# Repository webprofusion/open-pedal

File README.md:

# open-pedal

A cheap, open-source guitar audio dock: a USB-C class-compliant audio interface for any phone or tablet, with footswitches for bank and preset selection and an expression pedal input.

- Instrument in, stereo line out and a 6.35 mm headphone out
- 24-bit, 48 kHz USB audio (1 in, 2 out) plus USB MIDI on one cable
- Six footswitches: Bank −, Bank +, presets A to D
- RP2040, PCM1808 ADC, PCM5102A DAC; about US$52 in parts

The images are renders of the enclosure model, not photos.

Status: design stage. Nothing has been built or measured yet.

See [docs/design.md](docs/design.md) for the full hardware design.

## Layout

- `docs/`: design document and block diagram
- `hardware/`: pin map, schematic notes, BOM and `layout.json` (mechanical layout)
- `hardware/kicad/`: KiCad 10 project, generated by script: schematic and a placed, unrouted board
- `enclosure/`: Blender model of the enclosure, generated by script, with renders
- `firmware/`: RP2040 firmware (USB MIDI foot controller so far; audio not implemented)

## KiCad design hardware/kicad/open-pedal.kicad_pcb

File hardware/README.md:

# Hardware

Design inputs and the KiCad project for the open-pedal dock board. Nothing here has been built or measured.

- `pinmap.md`: RP2040 GPIO assignment (matches `firmware/src/pins.h`)
- `schematic-notes.md`: block-by-block connections and part values
- `bom.csv`: bill of materials with approximate prices
- `layout.json`: mechanical layout (enclosure, switch and rear-panel positions, device holder), shared by the board generator and the Blender enclosure model in `../enclosure/`
- `kicad/`: KiCad 10 project

See `../docs/design.md` for the reasoning behind the part choices.

## KiCad project

`kicad/open-pedal.kicad_pro` opens in KiCad 10. The schematic and board are generated from two files, so edit those and rebuild instead of editing the sheet by hand:

- `kicad/scripts/design.py`: every part, value, footprint and net
- `layout.json`: board size and where the connectors, headers and holes sit

Rebuild with the Python that ships with KiCad (it provides `pcbnew`):

```
"<KiCad 10>/bin/python" hardware/kicad/scripts/build.py
```

The build writes the schematic, runs ERC, exports KiCad's netlist and compares it pin by pin with `design.py`, writes the board, runs DRC, and exports a schematic PDF, a board render and a board GLB to `kicad/exports/`. It fails on any ERC violation, any netlist difference, or any DRC violation other than unrouted nets and silkscreen overlaps.

What is there:

- **Schematic**: 159 parts, 111 nets, one sheet. It is drawn netlist-style: parts are grouped by block and each pin carries a net label, so connections are by name and not by drawn wire.
- **Board**: 176 x 72 mm outline, 4 copper layers, every footprint placed with its nets assigned. Rear-panel connectors, switch headers and mounting holes are at their `layout.json` positions. The remaining parts are packed by block as a starting point.

What is not there:

- No routing, planes, stackup or design rules beyond KiCad's defaults. Decoupling capacitors are grouped with their block, not yet next to their pins.
- KiCad ships no 3D models for the Neutrik jacks and Alps pots, so they are missing from the board render. The Blender model draws stand-ins.

## Choices made at capture

`schematic-notes.md` leaves some parts open. The schematic picks these; all are unverified against current datasheets:

| Block | Choice |
| --- | --- |
| Boost converter | TPS61040, 10 uH, 360 k / 100 k feedback for about 5.7 V |
| 5 V analog LDO | TPS7A2050 (6.0 V maximum input, so the boost voltage must stay below that) |
| 3.3 V LDOs | AP2112K-3.3 (digital), LP5907-3.3 (analog) |
| 5 V input OR | Two B5819W Schottky diodes |
| Jacks | Neutrik NMJ4HCD2 (mono, switched) and NMJ6HCD2 (stereo, switched) |
| Pots | Alps RK09K (gain), RK09L dual (volume) |
| USB-C | GCT USB4105 (host), GCT USB4125 (power only) |
| Headphone amp | TPA6132A2, single-ended inputs, G0 = G1 = low for the lowest gain |
| Input jack | Tip switch contact to ground, so the input is shorted with nothing plugged in |
| R output detect | Sleeve switch contact to GPIO 7; reads high when a plug is in |
| Footswitches | Momentary with a single-colour LED ring, 12 mm bushing assumed; no particular part chosen |
| LED ring drive | V5 through 150 ohm, 2N7002 low-side switch per ring from GPIO 16 to 21 |
| Footswitch and OLED leads | JST XH headers, four-way |

The PCM1808 pin numbers in the project symbol library are from memory. Check them, and every pin strap, against the datasheets before ordering boards.

## To do

1. Breadboard proof with a Pico, a PCM1808 module and a PCM5102A module, wired to `pinmap.md`.
2. Check every symbol pin and strap against the current datasheets.
3. Confirm the connector heights in `layout.json` against the parts bought; they set the rear-panel drilling.
4. Place decoupling, route the 4-layer board, add ground planes and stackup.

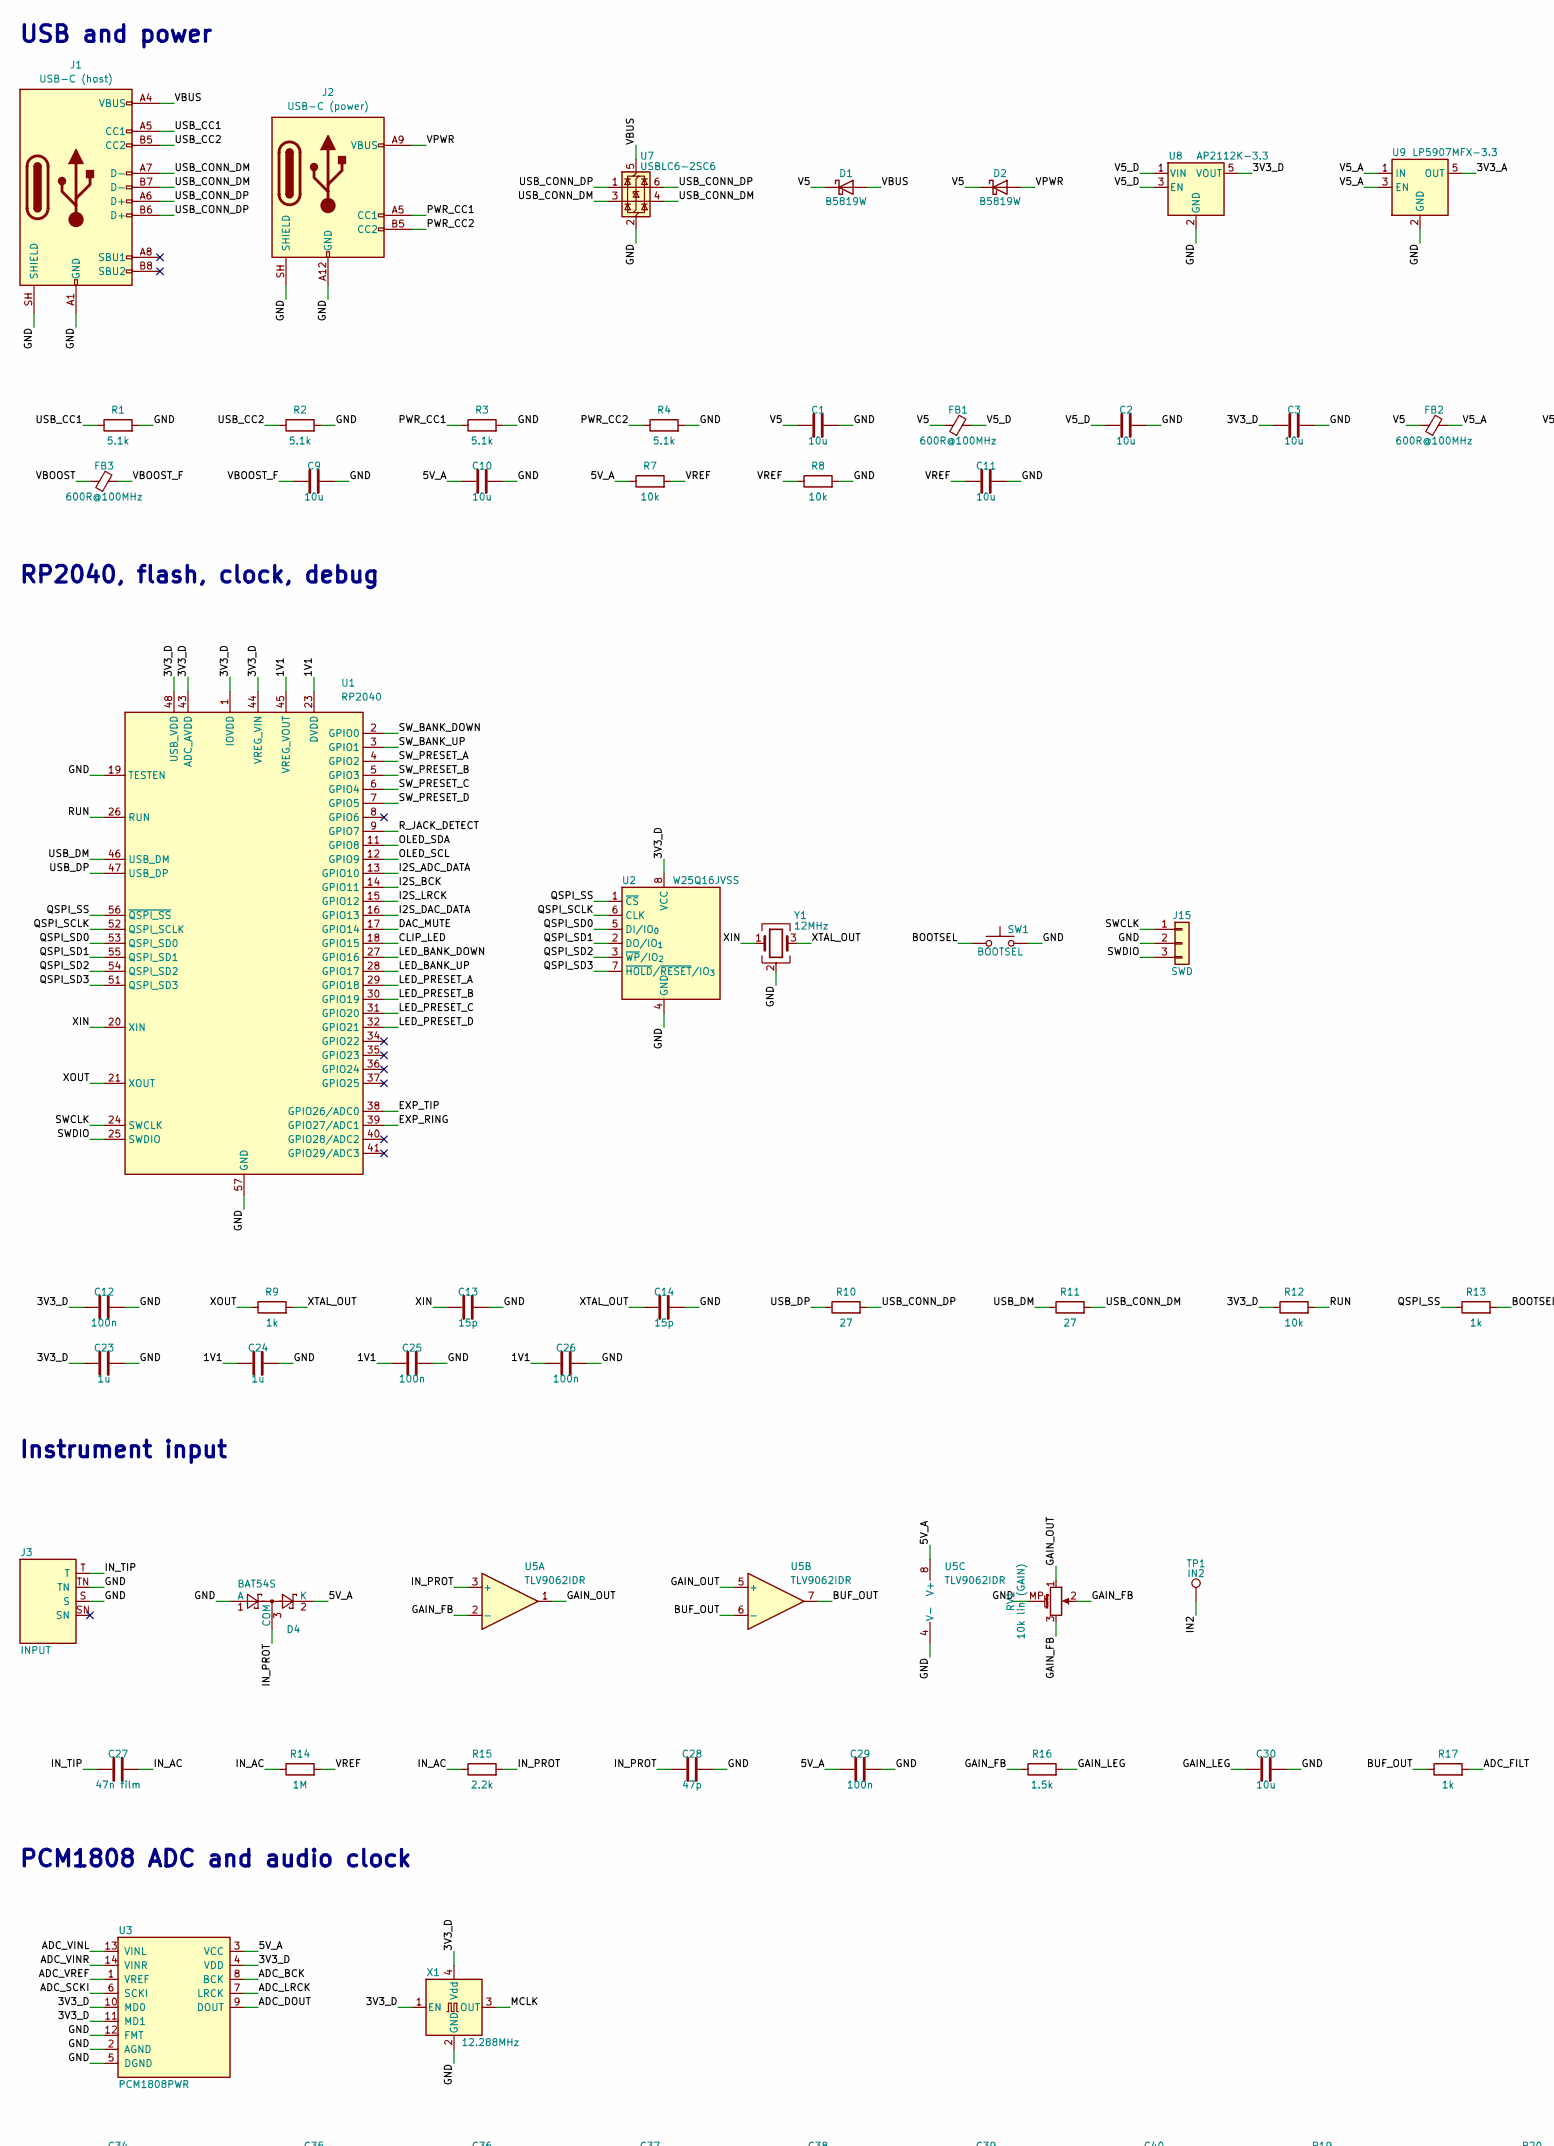
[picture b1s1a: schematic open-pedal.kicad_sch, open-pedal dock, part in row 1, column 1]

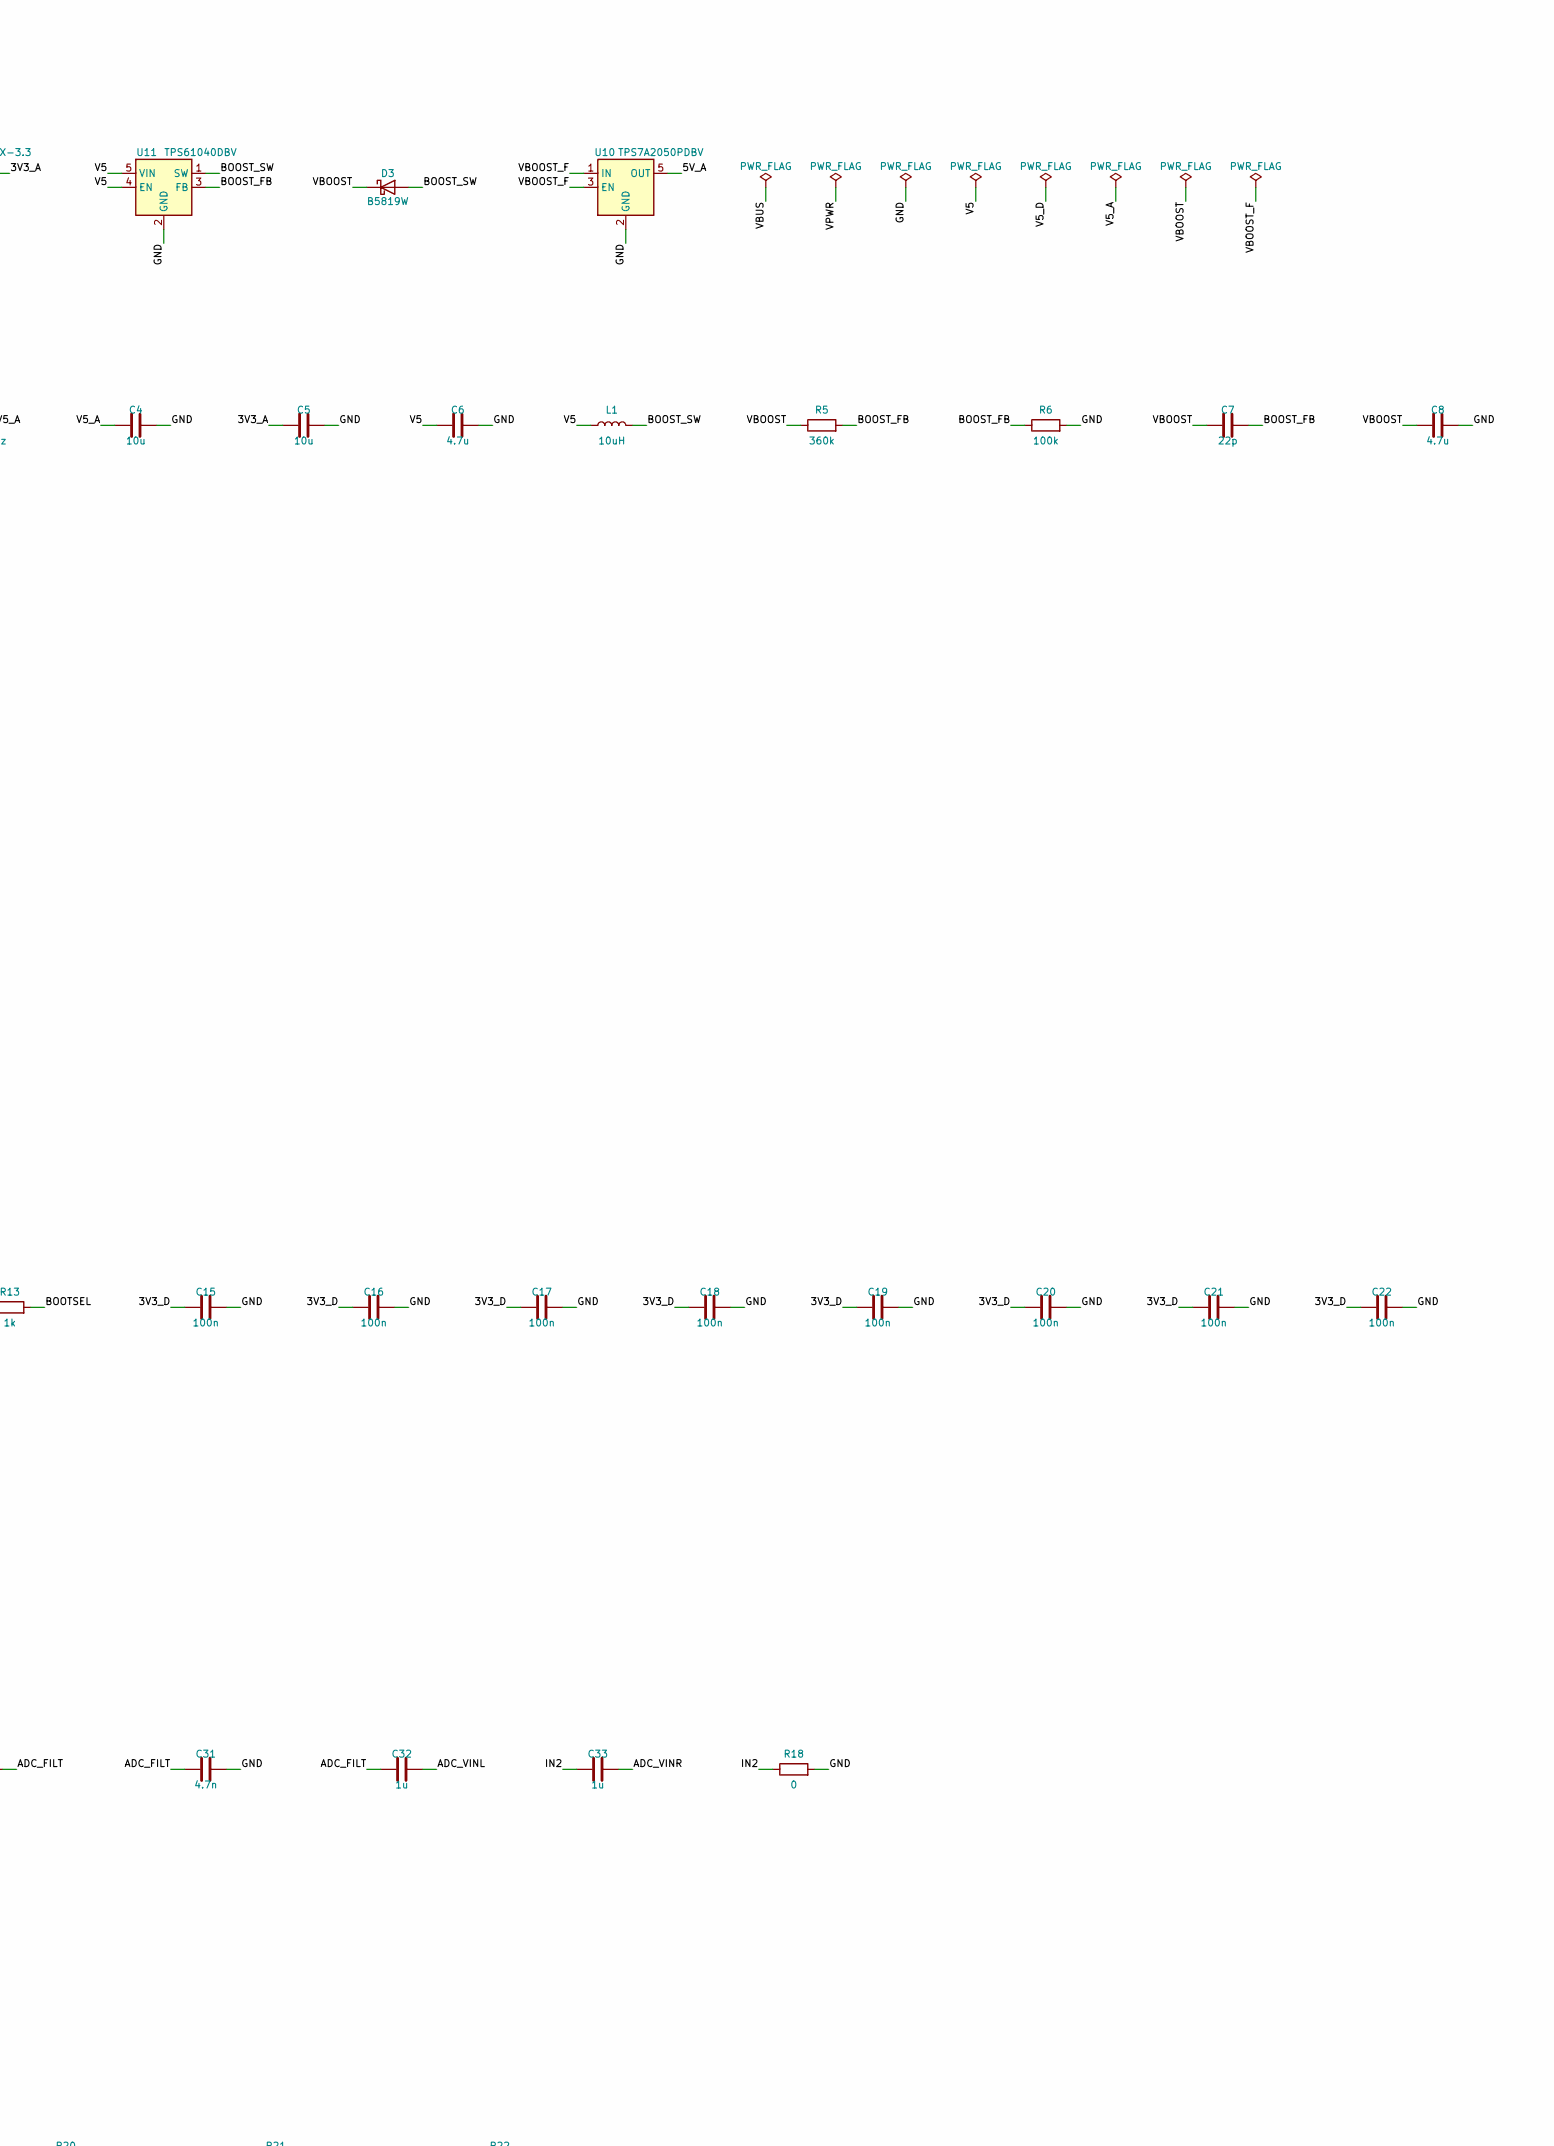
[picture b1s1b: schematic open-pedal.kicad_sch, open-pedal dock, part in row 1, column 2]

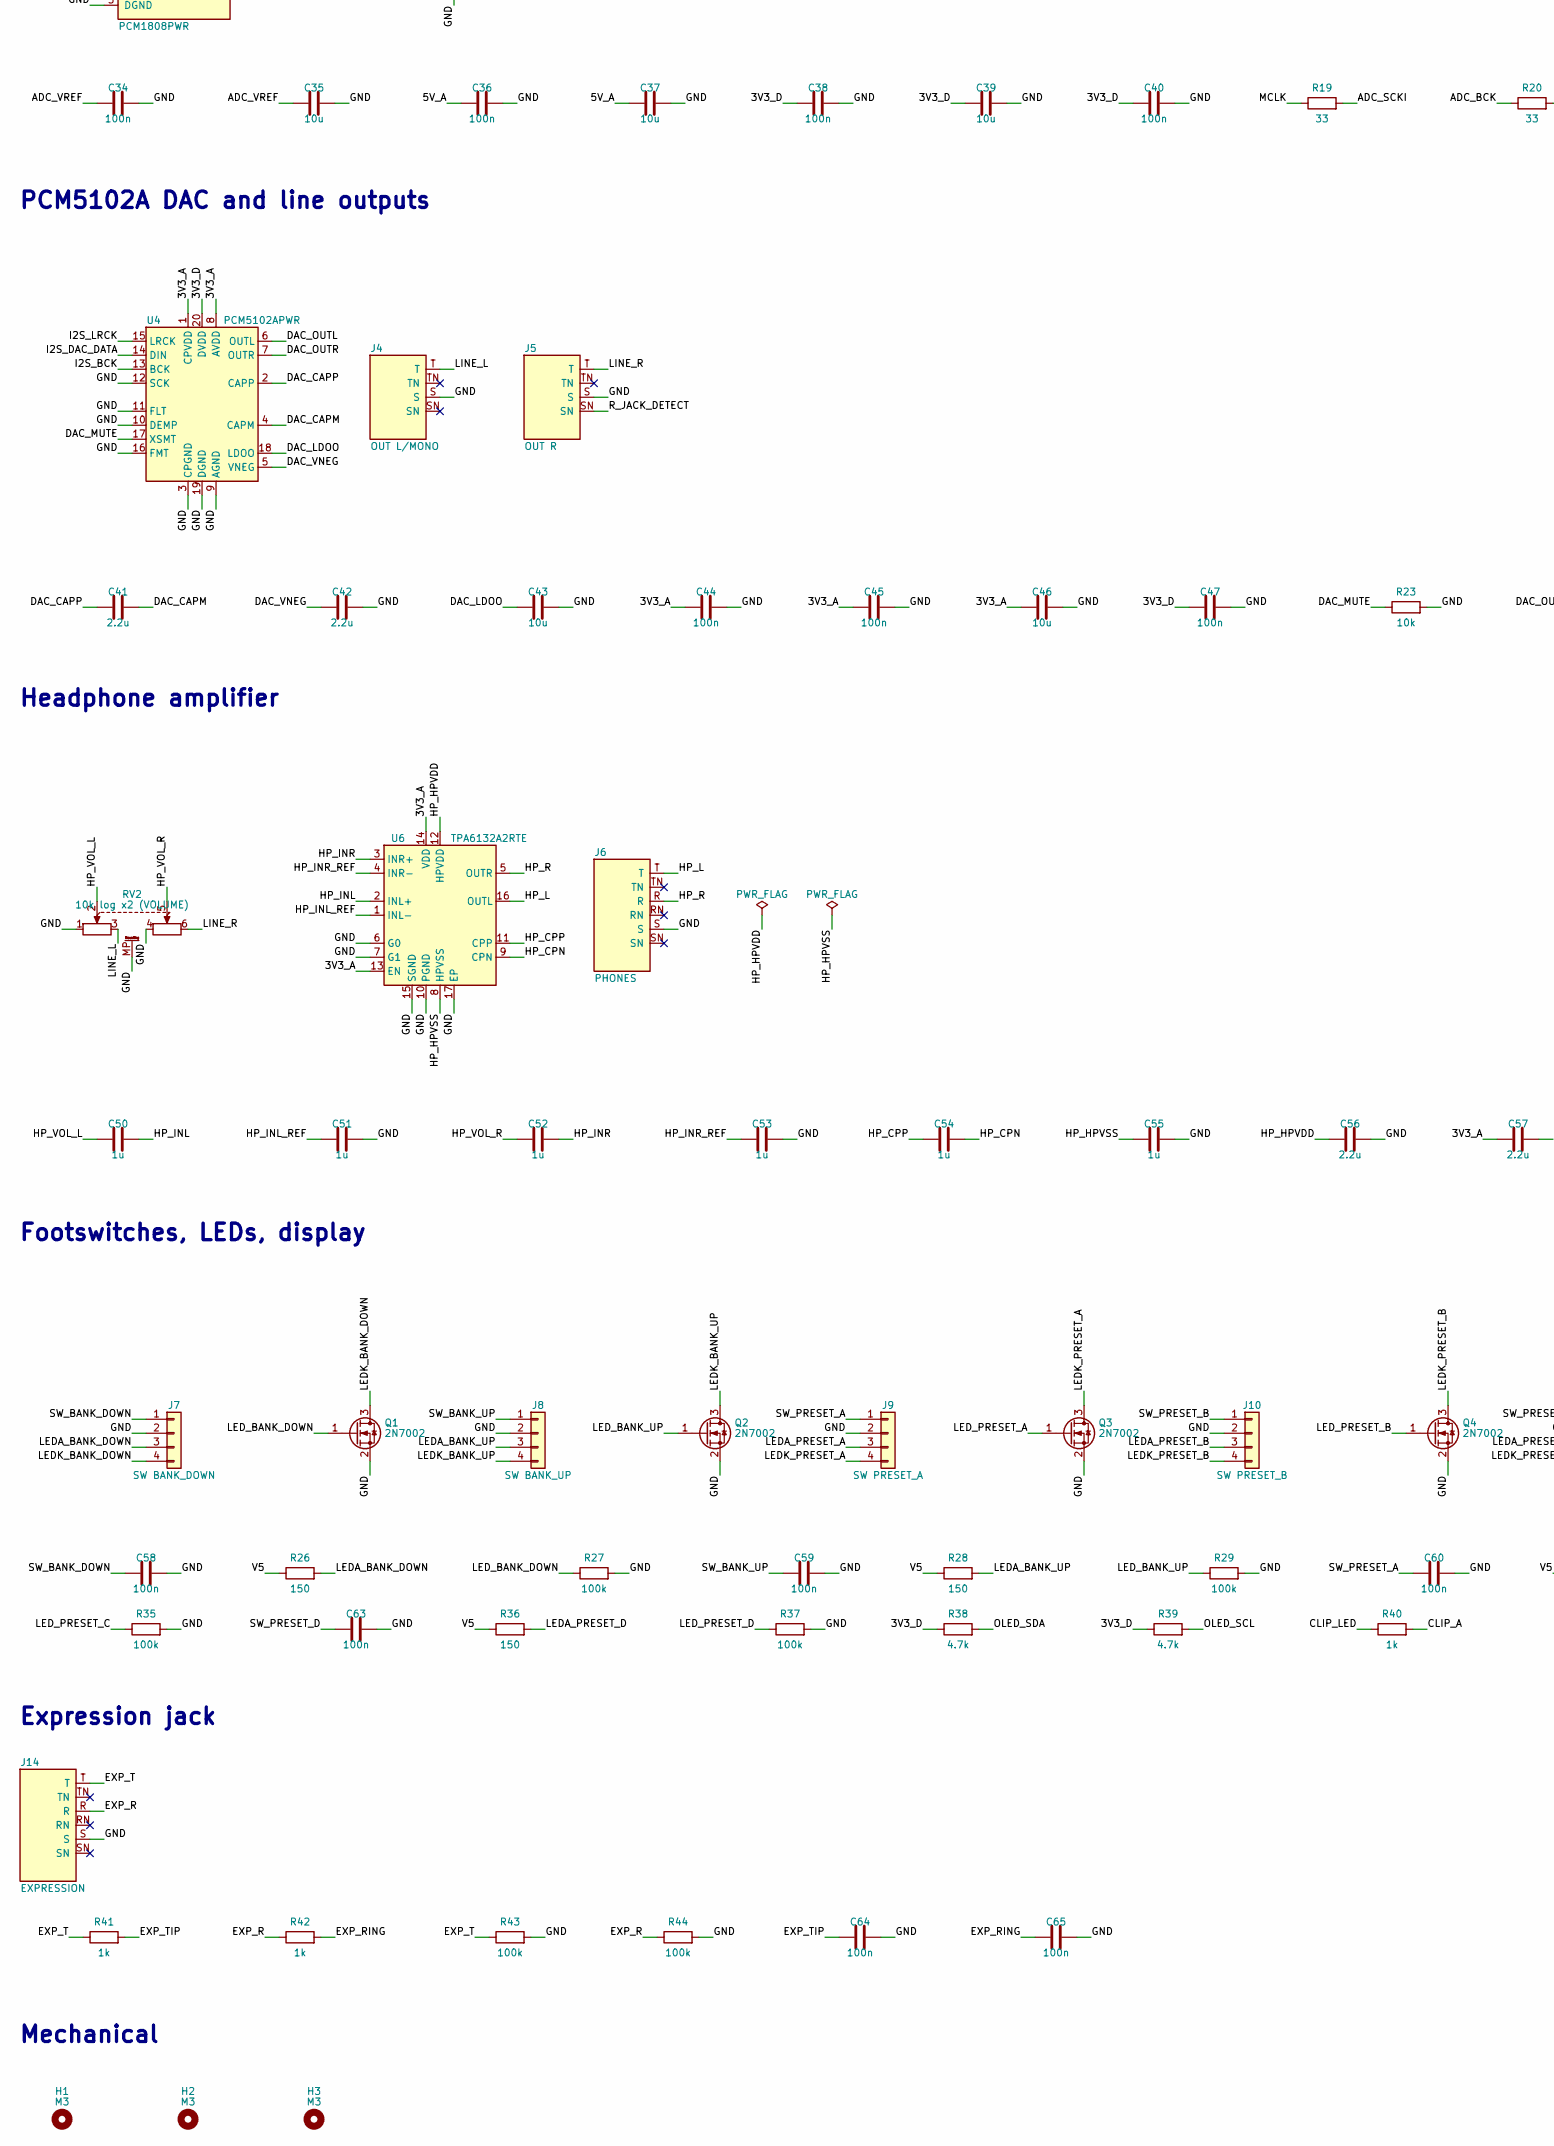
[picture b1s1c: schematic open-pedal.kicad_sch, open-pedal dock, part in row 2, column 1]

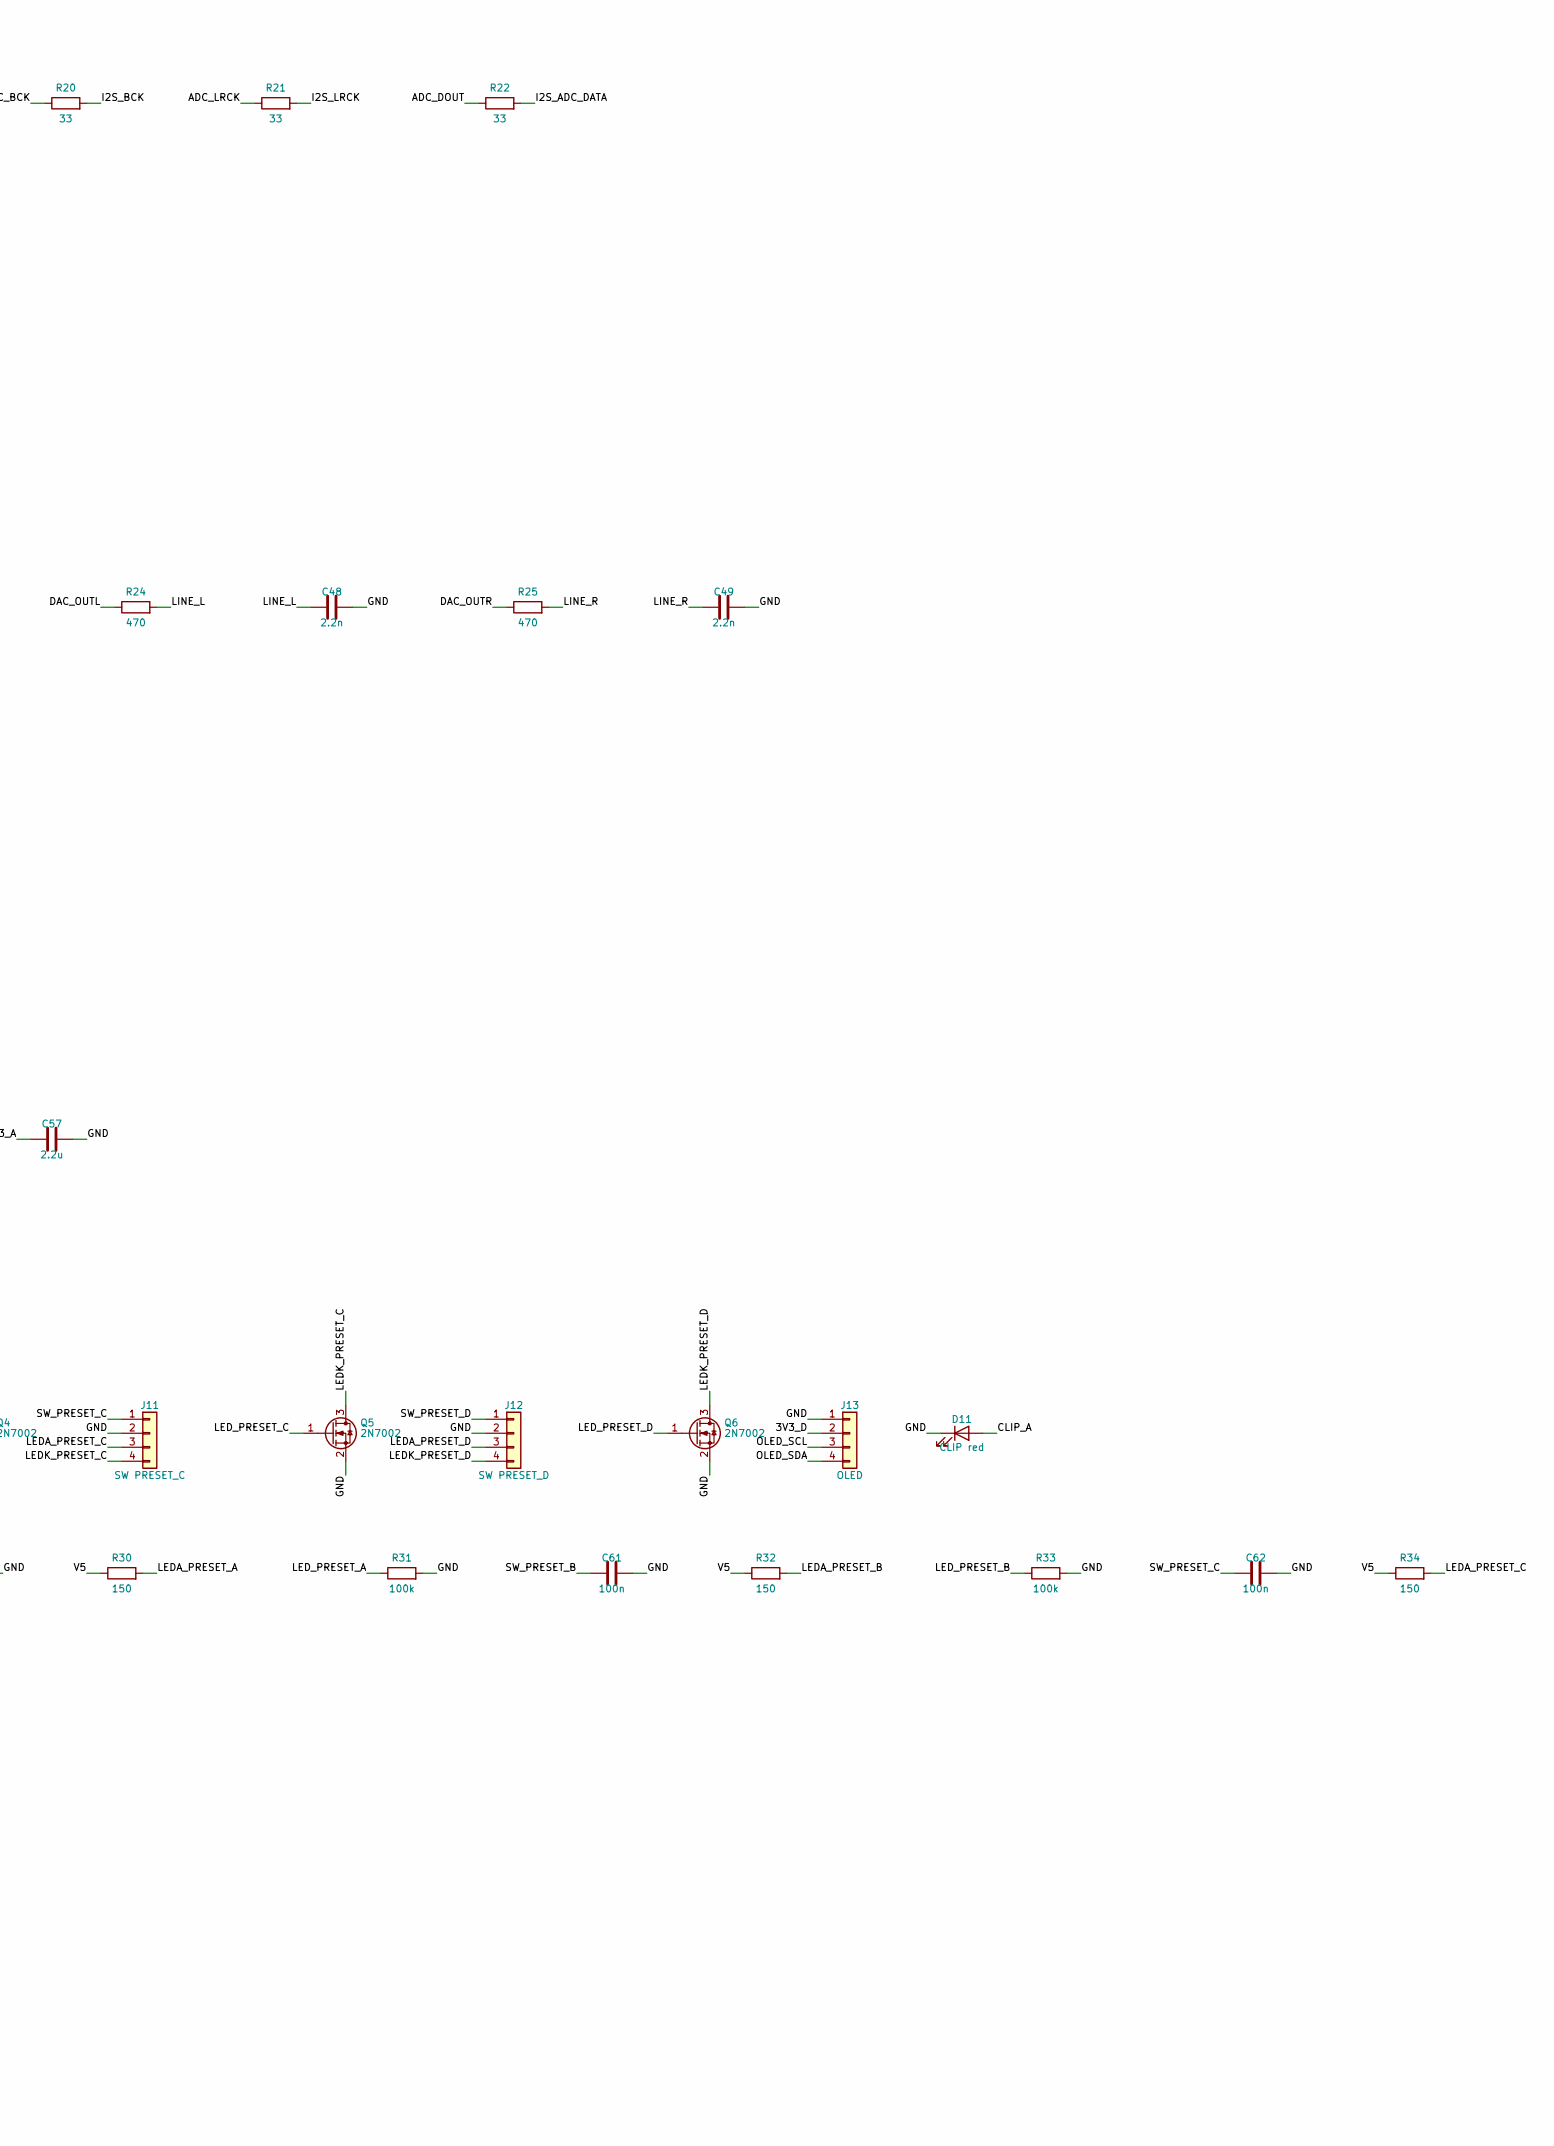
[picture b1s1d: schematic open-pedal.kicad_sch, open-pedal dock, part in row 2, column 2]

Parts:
C1, C2, C3, C4, C5, C9, C10, C11, C30, C35, C37, C39, C43, C46: 10u; C_0805_2012Metric
C6, C8: 4.7u; C_0805_2012Metric
C7: 22p; C_0603_1608Metric
C12, C15, C16, C17, C18, C19, C20, C21, C22, C25, C26, C29, C34, C36, C38, C40, C44, C45, C47, C58, C59, C60, C61, C62, C63, C64, C65: 100n; C_0603_1608Metric
C13, C14: 15p; C_0603_1608Metric
C23, C24, C32, C33, C50, C51, C52, C53, C54, C55: 1u; C_0603_1608Metric
C27: 47n film; C_1206_3216Metric
C28: 47p; C_0603_1608Metric
C31: 4.7n; C_0603_1608Metric
C41, C42, C56, C57: 2.2u; C_0805_2012Metric
C48, C49: 2.2n; C_0603_1608Metric
D1, D2, D3: B5819W; D_SOD-123
D4: BAT54S; SOT-23
D11: CLIP red; LED_0603_1608Metric
FB1, FB2, FB3: 600R@100MHz; L_0603_1608Metric
H1, H2, H3: M3; MountingHole_3.2mm_M3
J1: USB-C (host); USB_C_Receptacle_GCT_USB4105-xx-A_16P_TopMnt_Horizontal
J2: USB-C (power); USB_C_Receptacle_GCT_USB4125-xx-x_6P_TopMnt_Horizontal
J3: INPUT; Jack_6.35mm_Neutrik_NMJ4HCD2_Horizontal
J4: OUT L/MONO; Jack_6.35mm_Neutrik_NMJ4HCD2_Horizontal
J5: OUT R; Jack_6.35mm_Neutrik_NMJ4HCD2_Horizontal
J6: PHONES; Jack_6.35mm_Neutrik_NMJ6HCD2_Horizontal
J7: SW BANK_DOWN; JST_XH_B4B-XH-A_1x04_P2.50mm_Vertical
J8: SW BANK_UP; JST_XH_B4B-XH-A_1x04_P2.50mm_Vertical
J9: SW PRESET_A; JST_XH_B4B-XH-A_1x04_P2.50mm_Vertical
J10: SW PRESET_B; JST_XH_B4B-XH-A_1x04_P2.50mm_Vertical
J11: SW PRESET_C; JST_XH_B4B-XH-A_1x04_P2.50mm_Vertical
J12: SW PRESET_D; JST_XH_B4B-XH-A_1x04_P2.50mm_Vertical
J13: OLED; JST_XH_B4B-XH-A_1x04_P2.50mm_Vertical
J14: EXPRESSION; Jack_6.35mm_Neutrik_NMJ6HCD2_Horizontal
J15: SWD; PinHeader_1x03_P2.54mm_Vertical
L1: 10uH; L_Taiyo-Yuden_NR-30xx
Q1, Q2, Q3, Q4, Q5, Q6: 2N7002; SOT-23
R1, R2, R3, R4: 5.1k; R_0603_1608Metric
R5: 360k; R_0603_1608Metric
R6, R27, R29, R31, R33, R35, R37, R43, R44: 100k; R_0603_1608Metric
R7, R8, R12, R23: 10k; R_0603_1608Metric
R9, R13, R17, R40, R41, R42: 1k; R_0603_1608Metric
R10, R11: 27; R_0603_1608Metric
R14: 1M; R_0603_1608Metric
R15: 2.2k; R_0603_1608Metric
R16: 1.5k; R_0603_1608Metric
R18: 0; R_0603_1608Metric
R19, R20, R21, R22: 33; R_0603_1608Metric
R24, R25: 470; R_0603_1608Metric
R26, R28, R30, R32, R34, R36: 150; R_0603_1608Metric
R38, R39: 4.7k; R_0603_1608Metric
RV1: 10k lin (GAIN); Potentiometer_Alps_RK09K_Single_Horizontal
RV2: 10k log x2 (VOLUME); Potentiometer_Alps_RK09L_Double_Horizontal
SW1: BOOTSEL; SW_SPST_B3U-1000P
TP1: IN2; TestPoint_Pad_D1.5mm
U1: RP2040; QFN-56-1EP_7x7mm_P0.4mm_EP3.2x3.2mm
U2: W25Q16JVSS; SOIC-8_5.3x5.3mm_P1.27mm
U3: PCM1808PWR; TSSOP-14_4.4x5mm_P0.65mm
U4: PCM5102APWR; TSSOP-20_4.4x6.5mm_P0.65mm
U5: TLV9062IDR; SOIC-8_3.9x4.9mm_P1.27mm
U6: TPA6132A2RTE; WQFN-16-1EP_3x3mm_P0.5mm_EP1.6x1.6mm
U7: USBLC6-2SC6; SOT-23-6
U8: AP2112K-3.3; SOT-23-5
U9: LP5907MFX-3.3; SOT-23-5
U10: TPS7A2050PDBV; SOT-23-5
U11: TPS61040DBV; SOT-23-5
X1: 12.288MHz; Oscillator_SMD_Abracon_ASE-4Pin_3.2x2.5mm
Y1: 12MHz; Crystal_SMD_3225-4Pin_3.2x2.5mm

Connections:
1V1: C24.1, C25.1, C26.1, U1.23 (DVDD), U1.45 (VREG_VOUT), U1.50 (DVDD)
3V3_A: C5.1, C44.1, C45.1, C46.1, C57.1, U4.1 (CPVDD), U4.8 (AVDD), U6.13 (EN), U6.14 (VDD), U9.5 (OUT)
3V3_D: C3.1, C12.1, C15.1, C16.1, C17.1, C18.1, C19.1, C20.1, C21.1, C22.1, C23.1, C38.1, C39.1, C40.1, C47.1, J13.2, R12.1, R38.1, R39.1, U1.1 (IOVDD), U1.10 (IOVDD), U1.22 (IOVDD), U1.33 (IOVDD), U1.42 (IOVDD), U1.43 (ADC_AVDD), U1.44 (VREG_VIN), U1.48 (USB_VDD), U1.49 (IOVDD), U2.8 (VCC), U3.4 (VDD), U3.10 (MD0), U3.11 (MD1), U4.20 (DVDD), U8.5 (VOUT), X1.1 (EN), X1.4 (Vdd)
5V_A: C10.1, C29.1, C36.1, C37.1, D4.2 (K), R7.1, U3.3 (VCC), U5.8 (V+), U10.5 (OUT)
ADC_BCK: R20.1, U3.8 (BCK)
ADC_DOUT: R22.1, U3.9 (DOUT)
ADC_FILT: C31.1, C32.1, R17.2
ADC_LRCK: R21.1, U3.7 (LRCK)
ADC_SCKI: R19.2, U3.6 (SCKI)
ADC_VINL: C32.2, U3.13 (VINL)
ADC_VINR: C33.2, U3.14 (VINR)
ADC_VREF: C34.1, C35.1, U3.1 (VREF)
BOOST_FB: C7.2, R5.2, R6.1, U11.3 (FB)
BOOST_SW: D3.2 (A), L1.2, U11.1 (SW)
BOOTSEL: R13.2, SW1.1
BUF_OUT: R17.1, U5.6 (-), U5.7
CLIP_A: D11.2 (A), R40.2
CLIP_LED: R40.1, U1.18 (GPIO15)
DAC_CAPM: C41.2, U4.4 (CAPM)
DAC_CAPP: C41.1, U4.2 (CAPP)
DAC_LDOO: C43.1, U4.18 (LDOO)
DAC_MUTE: R23.1, U1.17 (GPIO14), U4.17 (XSMT)
DAC_OUTL: R24.1, U4.6 (OUTL)
DAC_OUTR: R25.1, U4.7 (OUTR)
DAC_VNEG: C42.1, U4.5 (VNEG)
EXP_R: J14.R, R42.1, R44.1
EXP_RING: C65.1, R42.2, U1.39 (GPIO27/ADC1)
EXP_T: J14.T, R41.1, R43.1
EXP_TIP: C64.1, R41.2, U1.38 (GPIO26/ADC0)
GAIN_FB: R16.1, RV1.2, RV1.3, U5.2 (-)
GAIN_LEG: C30.1, R16.2
GAIN_OUT: RV1.1, U5.1, U5.5 (+)
GND: C1.2, C2.2, C3.2, C4.2, C5.2, C6.2, C8.2, C9.2, C10.2, C11.2, C12.2, C13.2, C14.2, C15.2, C16.2, C17.2, C18.2, C19.2, C20.2, C21.2, C22.2, C23.2, C24.2, C25.2, C26.2, C28.2, C29.2, C30.2, C31.2, C34.2, C35.2, C36.2, C37.2, C38.2, C39.2, C40.2, C42.2, C43.2, C44.2, C45.2, C46.2, C47.2, C48.2, C49.2, C51.2, C53.2, C55.2, C56.2, C57.2, C58.2, C59.2, C60.2, C61.2, C62.2, C63.2, C64.2, C65.2, D4.1 (A), D11.1 (K), J1.A1 (GND), J1.A12 (GND), J1.B1 (GND), J1.B12 (GND), J1.SH (SHIELD), J2.A12 (GND), J2.B12 (GND), J2.SH (SHIELD), J3.S, J3.TN, J4.S, J5.S, J6.S, J7.2, J8.2, J9.2, J10.2, J11.2, J12.2, J13.1, J14.S, J15.2, Q1.2 (S), Q2.2 (S), Q3.2 (S), Q4.2 (S), Q5.2 (S), Q6.2 (S), R1.2, R2.2, R3.2, R4.2, R6.2, R8.2, R18.2, R23.2, R27.2, R29.2, R31.2, R33.2, R35.2, R37.2, R43.2, R44.2, RV1.MP (MountPin), RV2.1, RV2.4, RV2.MP (MountPin), SW1.2, U1.19 (TESTEN), U1.57 (GND), U2.4 (GND), U3.2 (AGND), U3.5 (DGND), U3.12 (FMT), U4.3 (CPGND), U4.9 (AGND), U4.10 (DEMP), U4.11 (FLT), U4.12 (SCK), U4.16 (FMT), U4.19 (DGND), U5.4 (V-), U6.6 (G0), U6.7 (G1), U6.10 (PGND), U6.15 (SGND), U6.17 (EP), U7.2 (GND), U8.2 (GND), U9.2 (GND), U10.2 (GND), U11.2 (GND), X1.2 (GND), Y1.2 (G), Y1.4 (G)
HP_CPN: C54.2, U6.9 (CPN)
HP_CPP: C54.1, U6.11 (CPP)
HP_HPVDD: C56.1, U6.12 (HPVDD)
HP_HPVSS: C55.1, U6.8 (HPVSS)
HP_INL: C50.2, U6.2 (INL+)
HP_INL_REF: C51.1, U6.1 (INL-)
HP_INR: C52.2, U6.3 (INR+)
HP_INR_REF: C53.1, U6.4 (INR-)
HP_L: J6.T, U6.16 (OUTL)
HP_R: J6.R, U6.5 (OUTR)
HP_VOL_L: C50.1, RV2.2
HP_VOL_R: C52.1, RV2.5
I2S_ADC_DATA: R22.2, U1.13 (GPIO10)
I2S_BCK: R20.2, U1.14 (GPIO11), U4.13 (BCK)
I2S_DAC_DATA: U1.16 (GPIO13), U4.14 (DIN)
I2S_LRCK: R21.2, U1.15 (GPIO12), U4.15 (LRCK)
IN2: C33.1, R18.1, TP1.1
IN_AC: C27.2, R14.1, R15.1
IN_PROT: C28.1, D4.3 (COM), R15.2, U5.3 (+)
IN_TIP: C27.1, J3.T
LEDA_BANK_DOWN: J7.3, R26.2
LEDA_BANK_UP: J8.3, R28.2
LEDA_PRESET_A: J9.3, R30.2
LEDA_PRESET_B: J10.3, R32.2
LEDA_PRESET_C: J11.3, R34.2
LEDA_PRESET_D: J12.3, R36.2
LEDK_BANK_DOWN: J7.4, Q1.3 (D)
LEDK_BANK_UP: J8.4, Q2.3 (D)
LEDK_PRESET_A: J9.4, Q3.3 (D)
LEDK_PRESET_B: J10.4, Q4.3 (D)
LEDK_PRESET_C: J11.4, Q5.3 (D)
LEDK_PRESET_D: J12.4, Q6.3 (D)
LED_BANK_DOWN: Q1.1 (G), R27.1, U1.27 (GPIO16)
LED_BANK_UP: Q2.1 (G), R29.1, U1.28 (GPIO17)
LED_PRESET_A: Q3.1 (G), R31.1, U1.29 (GPIO18)
LED_PRESET_B: Q4.1 (G), R33.1, U1.30 (GPIO19)
LED_PRESET_C: Q5.1 (G), R35.1, U1.31 (GPIO20)
LED_PRESET_D: Q6.1 (G), R37.1, U1.32 (GPIO21)
LINE_L: C48.1, J4.T, R24.2, RV2.3
LINE_R: C49.1, J5.T, R25.2, RV2.6
MCLK: R19.1, X1.3 (OUT)
OLED_SCL: J13.3, R39.2, U1.12 (GPIO9)
OLED_SDA: J13.4, R38.2, U1.11 (GPIO8)
PWR_CC1: J2.A5 (CC1), R3.1
PWR_CC2: J2.B5 (CC2), R4.1
QSPI_SCLK: U1.52 (QSPI_SCLK), U2.6 (CLK)
QSPI_SD0: U1.53 (QSPI_SD0), U2.5 (DI/IO_{0})
QSPI_SD1: U1.55 (QSPI_SD1), U2.2 (DO/IO_{1})
QSPI_SD2: U1.54 (QSPI_SD2), U2.3 (~WP/IO_{2})
QSPI_SD3: U1.51 (QSPI_SD3), U2.7 (~HOLD/~RESET/IO_{3})
QSPI_SS: R13.1, U1.56 (~QSPI_SS), U2.1 (~CS)
RUN: R12.2, U1.26 (RUN)
R_JACK_DETECT: J5.SN, U1.9 (GPIO7)
SWCLK: J15.1, U1.24 (SWCLK)
SWDIO: J15.3, U1.25 (SWDIO)
SW_BANK_DOWN: C58.1, J7.1, U1.2 (GPIO0)
SW_BANK_UP: C59.1, J8.1, U1.3 (GPIO1)
SW_PRESET_A: C60.1, J9.1, U1.4 (GPIO2)
SW_PRESET_B: C61.1, J10.1, U1.5 (GPIO3)
SW_PRESET_C: C62.1, J11.1, U1.6 (GPIO4)
SW_PRESET_D: C63.1, J12.1, U1.7 (GPIO5)
USB_CC1: J1.A5 (CC1), R1.1
USB_CC2: J1.B5 (CC2), R2.1
USB_CONN_DM: J1.A7 (D-), J1.B7 (D-), R11.2, U7.3 (I/O2), U7.4 (I/O2)
USB_CONN_DP: J1.A6 (D+), J1.B6 (D+), R10.2, U7.1 (I/O1), U7.6 (I/O1)
USB_DM: R11.1, U1.46 (USB_DM)
USB_DP: R10.1, U1.47 (USB_DP)
V5: C1.1, C6.1, D1.1 (K), D2.1 (K), FB1.1, FB2.1, L1.1, R26.1, R28.1, R30.1, R32.1, R34.1, R36.1, U11.4 (EN), U11.5 (VIN)
V5_A: C4.1, FB2.2, U9.1 (IN), U9.3 (EN)
V5_D: C2.1, FB1.2, U8.1 (VIN), U8.3 (EN)
VBOOST: C7.1, C8.1, D3.1 (K), FB3.1, R5.1
VBOOST_F: C9.1, FB3.2, U10.1 (IN), U10.3 (EN)
VBUS: D1.2 (A), J1.A4 (VBUS), J1.A9 (VBUS), J1.B4 (VBUS), J1.B9 (VBUS), U7.5 (VBUS)
VPWR: D2.2 (A), J2.A9 (VBUS), J2.B9 (VBUS)
VREF: C11.1, R7.2, R8.1, R14.2
XIN: C13.1, U1.20 (XIN), Y1.1
XOUT: R9.1, U1.21 (XOUT)
XTAL_OUT: C14.1, R9.2, Y1.3

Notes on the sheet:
USB and power
RP2040, flash, clock, debug
Instrument input
PCM1808 ADC and audio clock
PCM5102A DAC and line outputs
Headphone amplifier
Footswitches, LEDs, display
Expression jack
Mechanical

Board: 4 copper layers, 159 parts (0 on the bottom side), 111 nets, no tracks yet.

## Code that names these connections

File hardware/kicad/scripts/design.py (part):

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      "USB_DP": "USB_DP", "USB_DM": "USB_DM",
      "~{QSPI_SS}": "QSPI_SS", "QSPI_SCLK": "QSPI_SCLK", "QSPI_SD0": "QSPI_SD0",
      "QSPI_SD1": "QSPI_SD1", "QSPI_SD2": "QSPI_SD2", "QSPI_SD3": "QSPI_SD3",
      "GPIO0": "SW_BANK_DOWN", "GPIO1": "SW_BANK_UP", "GPIO2": "SW_PRESET_A",
      "GPIO3": "SW_PRESET_B", "GPIO4": "SW_PRESET_C", "GPIO5": "SW_PRESET_D",
      "GPIO6": "NC", "GPIO7": "R_JACK_DETECT", "GPIO8": "OLED_SDA", "GPIO9": "OLED_SCL",
      "GPIO10": "I2S_ADC_DATA", "GPIO11": "I2S_BCK", "GPIO12": "I2S_LRCK",
      "GPIO13": "I2S_DAC_DATA", "GPIO14": "DAC_MUTE", "GPIO15": "CLIP_LED",
      "GPIO26/ADC0": "EXP_TIP", "GPIO27/ADC1": "EXP_RING",
      "GPIO28/ADC2": "NC", "GPIO29/ADC3": "NC"}
for g, name in zip(range(16, 22), ("BANK_DOWN", "BANK_UP", "PRESET_A", "PRESET_B", "PRESET_C", "PRESET_D")):
    rp[f"GPIO{g}"] = f"LED_{name}"
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
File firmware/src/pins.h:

// GPIO assignment for the open-pedal dock (RP2040).
// Keep in step with hardware/pinmap.md.
#ifndef PINS_H
#define PINS_H

// Footswitches: momentary to ground, internal pull-ups.
#define PIN_SW_BANK_DOWN   0
#define PIN_SW_BANK_UP     1
#define PIN_SW_PRESET_A    2
#define PIN_SW_PRESET_B    3
#define PIN_SW_PRESET_C    4
#define PIN_SW_PRESET_D    5

// GPIO 6 is spare.
#define PIN_R_JACK_DETECT  7   // needs the internal pull-up; high when a plug is in the R output jack
#define PIN_OLED_SDA       8   // I2C0
#define PIN_OLED_SCL       9

// I2S: the PCM1808 is clock master. These three must stay consecutive,
// the PIO programs address BCK and LRCK relative to the ADC data pin.
#define PIN_I2S_ADC_DATA   10
#define PIN_I2S_BCK        11
#define PIN_I2S_LRCK       12
#define PIN_I2S_DAC_DATA   13

#define PIN_DAC_MUTE       14  // PCM5102A XSMT: low = muted
#define PIN_CLIP_LED       15

// Footswitch LED rings: high = lit, one low-side driver each. PWM-capable for dimming.
#define PIN_LED_BANK_DOWN  16
#define PIN_LED_BANK_UP    17
#define PIN_LED_PRESET_A   18
#define PIN_LED_PRESET_B   19
#define PIN_LED_PRESET_C   20
#define PIN_LED_PRESET_D   21

// Expression jack: tip and ring each through 1 k.
#define PIN_EXP_TIP        26  // ADC0
#define PIN_EXP_RING       27  // ADC1
#define ADC_CH_EXP_TIP     0
#define ADC_CH_EXP_RING    1

#endif
